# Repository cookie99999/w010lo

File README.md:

# A homebrew MC68010 computer

### Current specs:

- 16MHz 68010
- 1MB RAM
- 256K flash
- 68681 DUART
- A simple monitor ported from my 65816 computer, with XMODEM download support
- PATA interface (tested with several CF cards and a real IDE HDD)

### Todo:

- New PCB revision with some bodge fixes and some SMD parts to fit more memory
- Real-time clock
- Audio+video board
- PS/2 mouse + keyboard controller
- Consider networking (SLIP or ethernet controller)

### Toolchain notes

For assembly I am using vasm, since I like the syntax better than GAS. For C, I built a cross-compiling GCC and binutils from source. When configuring GCC for a 68000/68008/68010 target, you have to be careful not to let it use any 68020+ or FPU specific instructions, or else your libgcc won't work. Here's the line I used to configure mine:
```
../gcc-15.2.0/configure --prefix=/home/cookie/.local/ --program-prefix=m68k-elf- --target=m68k-elf --with-cpu=m68000 --enable-languages=c --with-newlib --disable-libssp --disable-libgomp --disable-threads --disable-multilib --disable-nls --disable-libquadmath --without-headers --disable-m68020 --disable-m68881
```
Some of the less obvious options may not be strictly necessary, I haven't tested with and without each one.
With just a compiler, binutils, and libgcc, you have pretty much all you need to comfortably write and use C programs. I have ported newlib+libgloss, but have some minor bugs to work out. I will eventually write up the process, as a lot of the documentation online is outdated by this point.

###

Shoutout to [aslak](https://www.aslak.net/), [rosco-m68k](https://github.com/rosco-m68k), [68-Katy](https://www.bigmessowires.com/68-katy/), [Matt Sarnoff](https://github.com/74hc595/68k-nano), [Jeff Tranter](https://jefftranter.blogspot.com/), and [Mackerel-68k](https://hackaday.io/project/183861-mackerel-68k-linux-sbcs) for their inspiring projects and helpful logs.

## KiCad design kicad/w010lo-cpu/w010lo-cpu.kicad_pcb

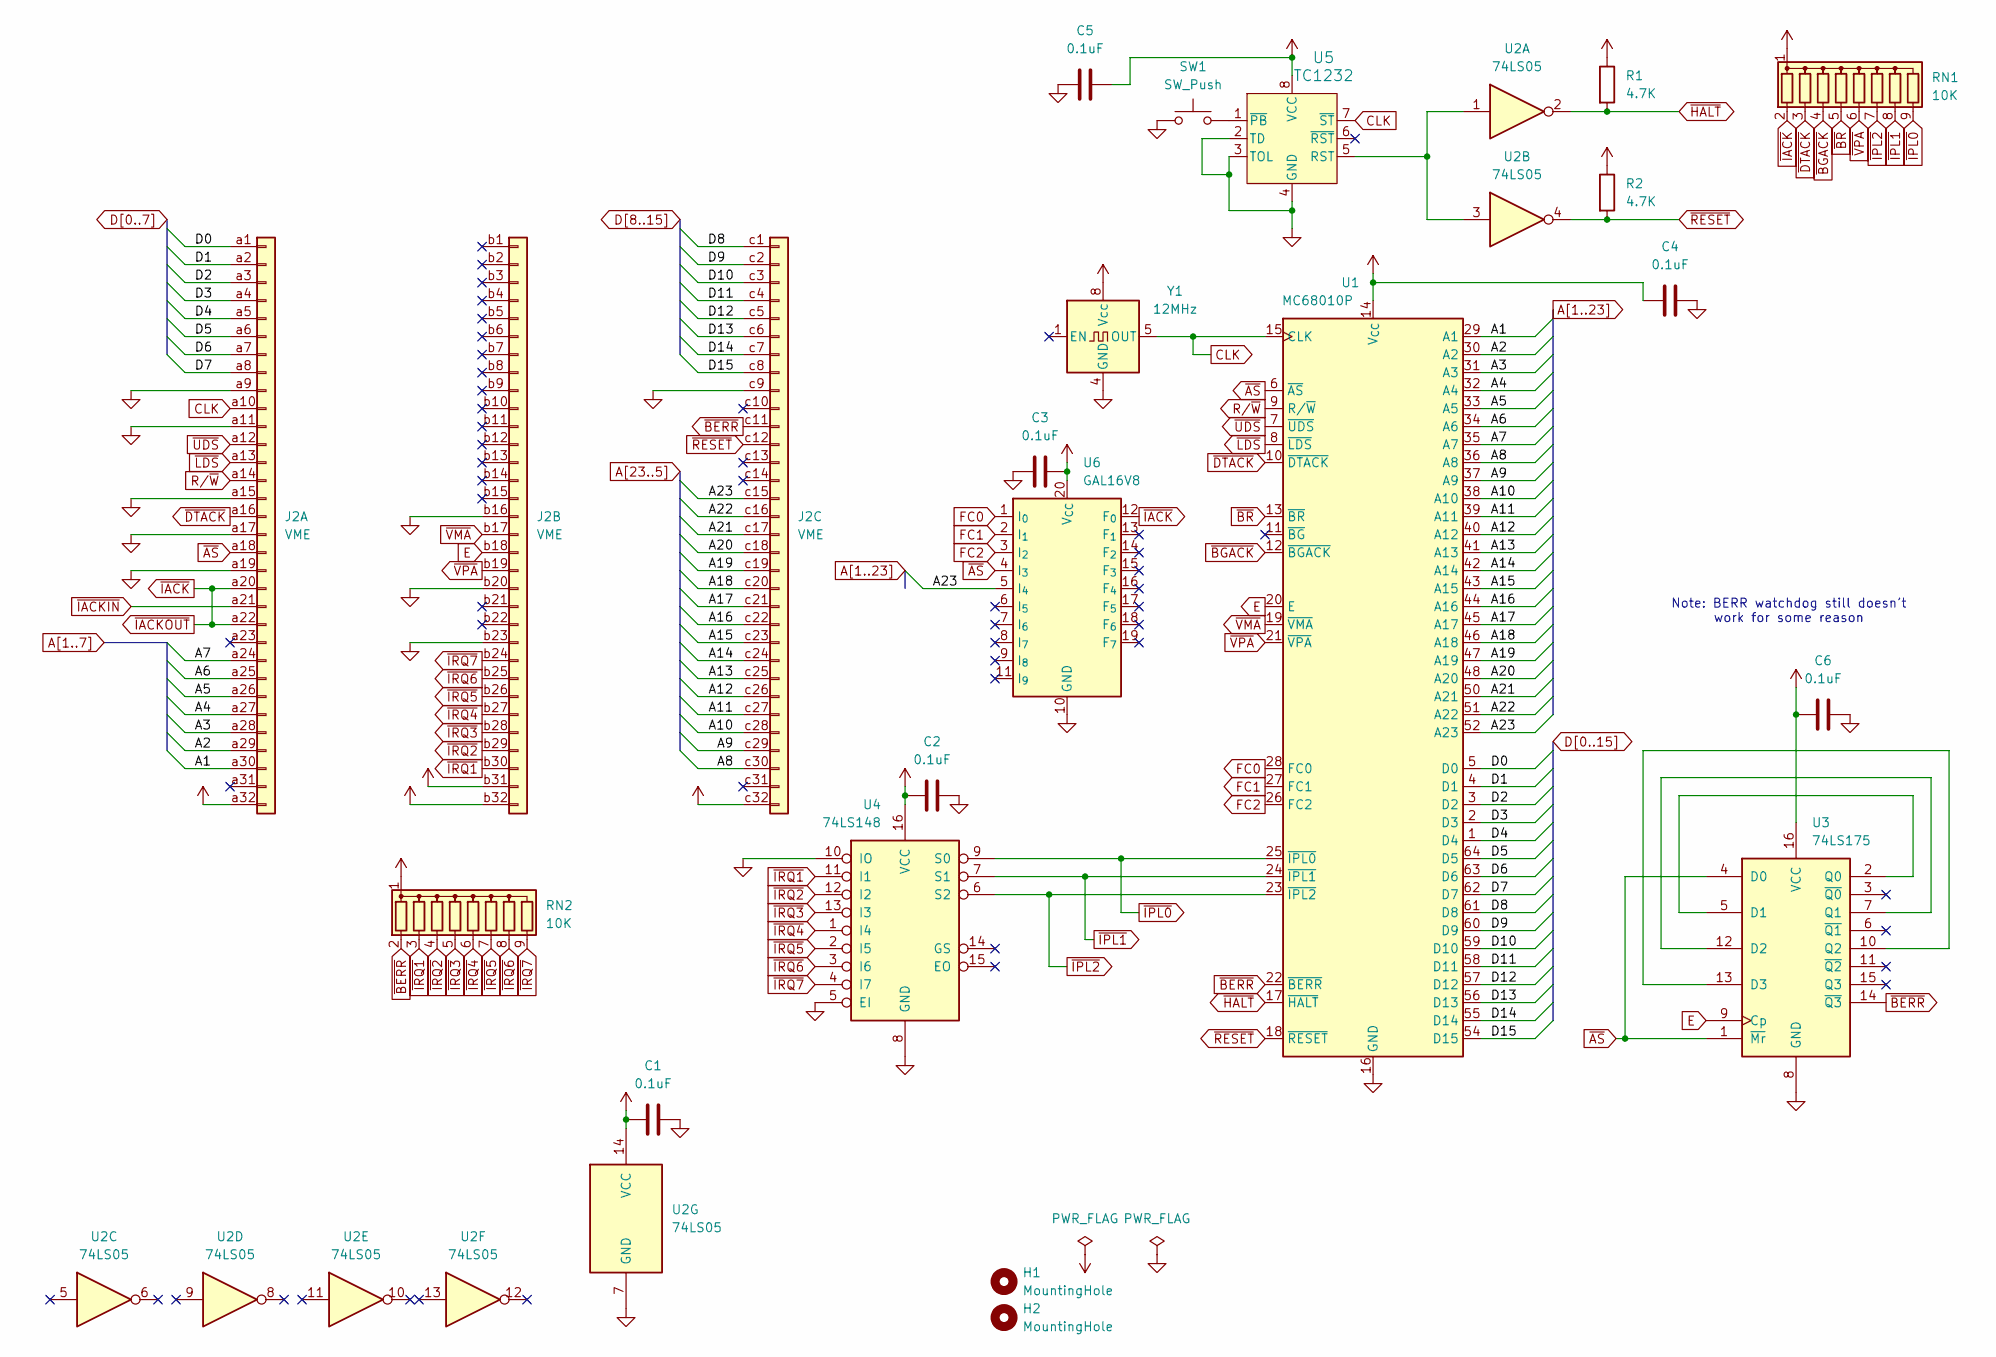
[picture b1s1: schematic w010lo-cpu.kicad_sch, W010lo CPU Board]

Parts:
C1, C2, C3, C4, C5, C6: 0.1uF; C_Disc_D5.0mm_W2.5mm_P5.00mm
H1, H2: MountingHole; MountingHole_3.2mm_M3
J2: VME; DIN41612_C_3x32_Male_Horizontal_THT
R1, R2: 4.7K; R_Axial_DIN0204_L3.6mm_D1.6mm_P5.08mm_Horizontal
RN1, RN2: 10K; R_Array_SIP9
SW1: SW_Push; SW_TS11-674-135-BK-160-RA-D
U1: MC68010P; DIP-64_W22.86mm
U2: 74LS05; DIP-14_W7.62mm_Socket
U3: 74LS175; DIP-16_W7.62mm_Socket
U4: 74LS148; DIP-16_W7.62mm_Socket
U5: TC1232; DIP-8_W7.62mm_Socket
U6: GAL16V8; DIP-20_W7.62mm_Socket
Y1: 12MHz; Oscillator_DIP-8

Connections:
A1: J2.a30, U1.29 (A1)
A2: J2.a29, U1.30 (A2)
A3: J2.a28, U1.31 (A3)
A4: J2.a27, U1.32 (A4)
A5: J2.a26, U1.33 (A5)
A6: J2.a25, U1.34 (A6)
A7: J2.a24, U1.35 (A7)
A8: J2.c30, U1.36 (A8)
A9: J2.c29, U1.37 (A9)
A10: J2.c28, U1.38 (A10)
A11: J2.c27, U1.39 (A11)
A12: J2.c26, U1.40 (A12)
A13: J2.c25, U1.41 (A13)
A14: J2.c24, U1.42 (A14)
A15: J2.c23, U1.43 (A15)
A16: J2.c22, U1.44 (A16)
A17: J2.c21, U1.45 (A17)
A18: J2.c20, U1.46 (A18)
A19: J2.c19, U1.47 (A19)
A20: J2.c18, U1.48 (A20)
A21: J2.c17, U1.50 (A21)
A22: J2.c16, U1.51 (A22)
A23: J2.c15, U1.52 (A23), U6.5 (I_{4})
CLK: J2.a10, U1.15 (CLK), U5.7 (~ST), Y1.5 (OUT)
D0: J2.a1, U1.5 (D0)
D1: J2.a2, U1.4 (D1)
D2: J2.a3, U1.3 (D2)
D3: J2.a4, U1.2 (D3)
D4: J2.a5, U1.1 (D4)
D5: J2.a6, U1.64 (D5)
D6: J2.a7, U1.63 (D6)
D7: J2.a8, U1.62 (D7)
D8: J2.c1, U1.61 (D8)
D9: J2.c2, U1.60 (D9)
D10: J2.c3, U1.59 (D10)
D11: J2.c4, U1.58 (D11)
D12: J2.c5, U1.57 (D12)
D13: J2.c6, U1.56 (D13)
D14: J2.c7, U1.55 (D14)
D15: J2.c8, U1.54 (D15)
E: J2.b18, U1.20 (E), U3.9 (Cp)
FC0: U1.28 (FC0), U6.1 (I_{0})
FC1: U1.27 (FC1), U6.2 (I_{1})
FC2: U1.26 (FC2), U6.3 (I_{2})
GND: C1.2, C2.2, C3.2, C4.2, C5.2, C6.2, J2.a9, J2.a11, J2.a15, J2.a17, J2.a19, J2.b16, J2.b20, J2.b23, J2.c9, SW1.1, U1.16 (GND), U1.53 (GND), U2.7 (GND), U3.8 (GND), U4.5 (EI), U4.8 (GND), U4.10 (IO), U5.2 (TD), U5.3 (TOL), U5.4 (GND), U6.10 (GND), Y1.4 (GND)
unnamed: U3.2 (Q0), U3.5 (D1)
unnamed: U3.7 (Q1), U3.12 (D2)
unnamed: U3.10 (Q2), U3.13 (D3)
unnamed: U2.1, U2.3, U5.5 (RST)
unnamed: SW1.2, U5.1 (~PB)
R/~W: J2.a14, U1.9 (R/~W)
VCC: C1.1, C2.1, C3.1, C4.1, C5.1, C6.1, J2.a32, J2.b31, J2.b32, J2.c32, R1.1, R2.1, RN1.1 (common), RN2.1 (common), U1.14 (V_{CC}), U1.49 (V_{CC}), U2.14 (VCC), U3.16 (VCC), U4.16 (VCC), U5.8 (VCC), U6.20 (V_{CC}), Y1.8 (Vcc)
~AS: J2.a18, U1.6 (~AS), U3.1 (~Mr), U3.4 (D0), U6.4 (I_{3})
~BERR: J2.c11, RN2.2 (R1), U1.22 (~BERR), U3.14 (~Q3)
~BGACK: RN1.4 (R3), U1.12 (~BGACK)
~BR: RN1.5 (R4), U1.13 (~BR)
~DTACK: J2.a16, RN1.3 (R2), U1.10 (~DTACK)
~HALT: R1.2, U1.17 (~HALT), U2.2
~IACKIN: J2.a21
~IACKOUT: J2.a20, J2.a22, RN1.2 (R1), U6.12 (F_{0})
~IPL0: RN1.9 (R8), U1.25 (~IPL0), U4.9 (S0)
~IPL1: RN1.8 (R7), U1.24 (~IPL1), U4.7 (S1)
~IPL2: RN1.7 (R6), U1.23 (~IPL2), U4.6 (S2)
~IRQ1: J2.b30, RN2.3 (R2), U4.11 (I1)
~IRQ2: J2.b29, RN2.4 (R3), U4.12 (I2)
~IRQ3: J2.b28, RN2.5 (R4), U4.13 (I3)
~IRQ4: J2.b27, RN2.6 (R5), U4.1 (I4)
~IRQ5: J2.b26, RN2.7 (R6), U4.2 (I5)
~IRQ6: J2.b25, RN2.8 (R7), U4.3 (I6)
~IRQ7: J2.b24, RN2.9 (R8), U4.4 (I7)
~LDS: J2.a13, U1.8 (~LDS)
~RESET: J2.c12, R2.2, U1.18 (~RESET), U2.4
~UDS: J2.a12, U1.7 (~UDS)
~VMA: J2.b17, U1.19 (~VMA)
~VPA: J2.b19, RN1.6 (R5), U1.21 (~VPA)

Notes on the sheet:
Note: BERR watchdog still doesn't work for some reason

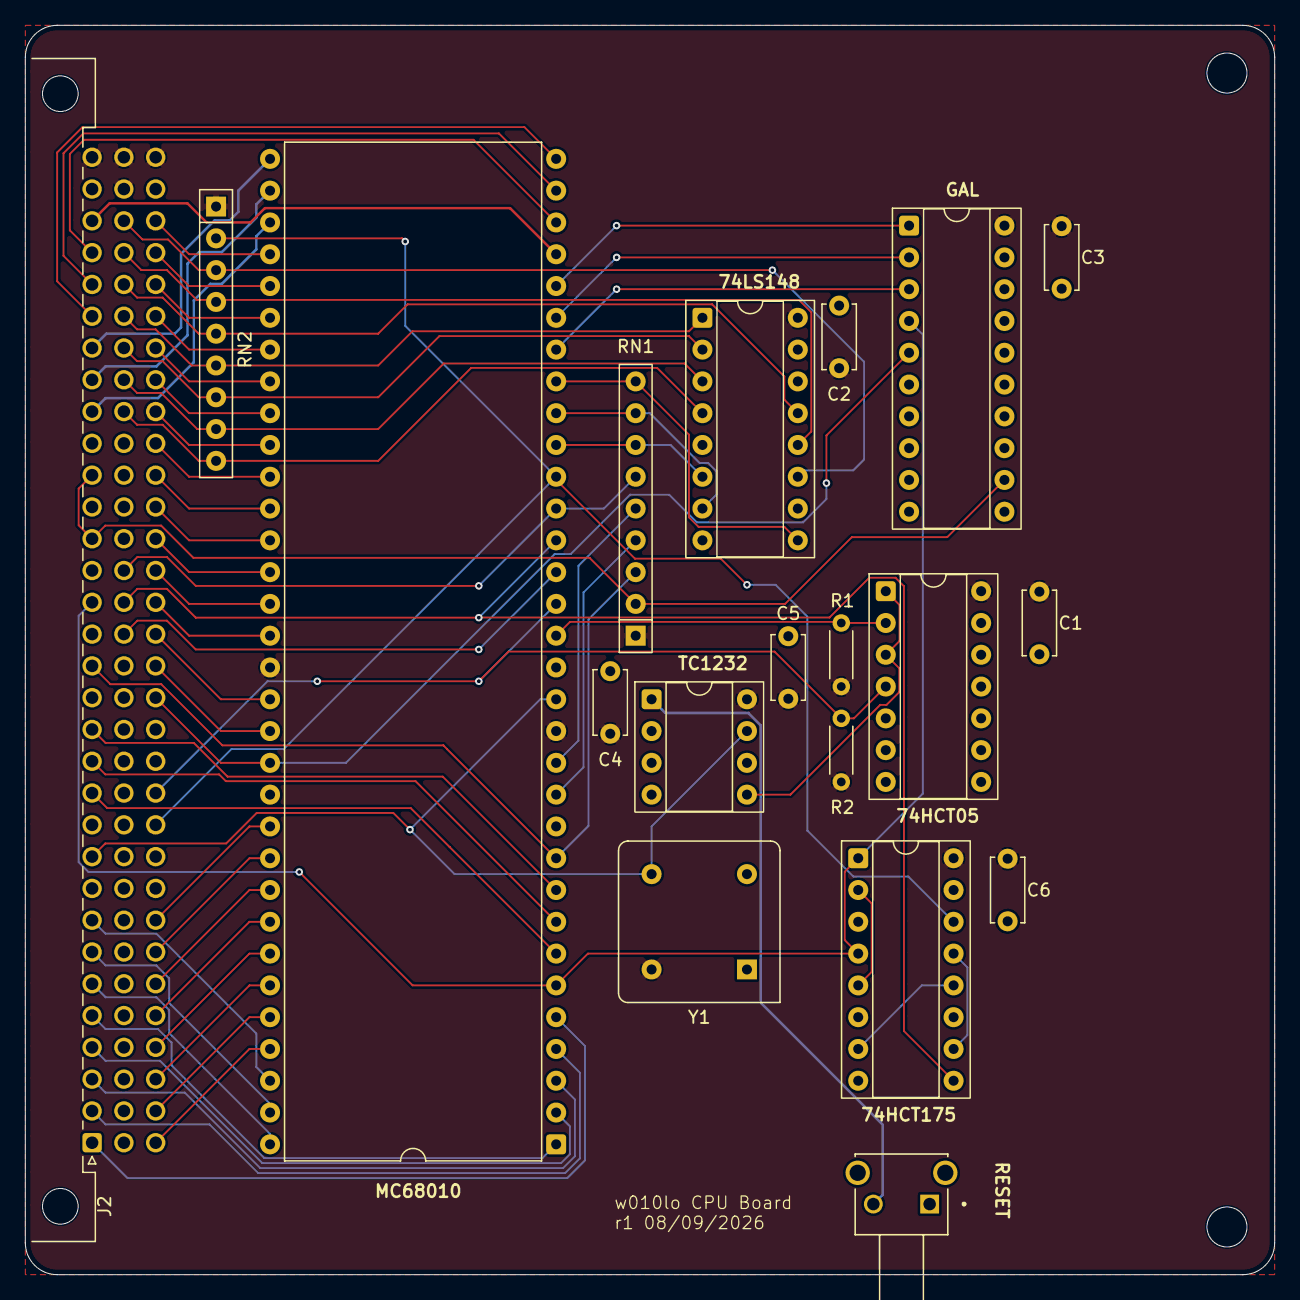
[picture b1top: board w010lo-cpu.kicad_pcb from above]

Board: 4 copper layers, 99.8 x 99.8 mm, 22 parts (0 on the bottom side), 74 nets.

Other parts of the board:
H3: MountingHole; MountingHole_3.2mm_M3

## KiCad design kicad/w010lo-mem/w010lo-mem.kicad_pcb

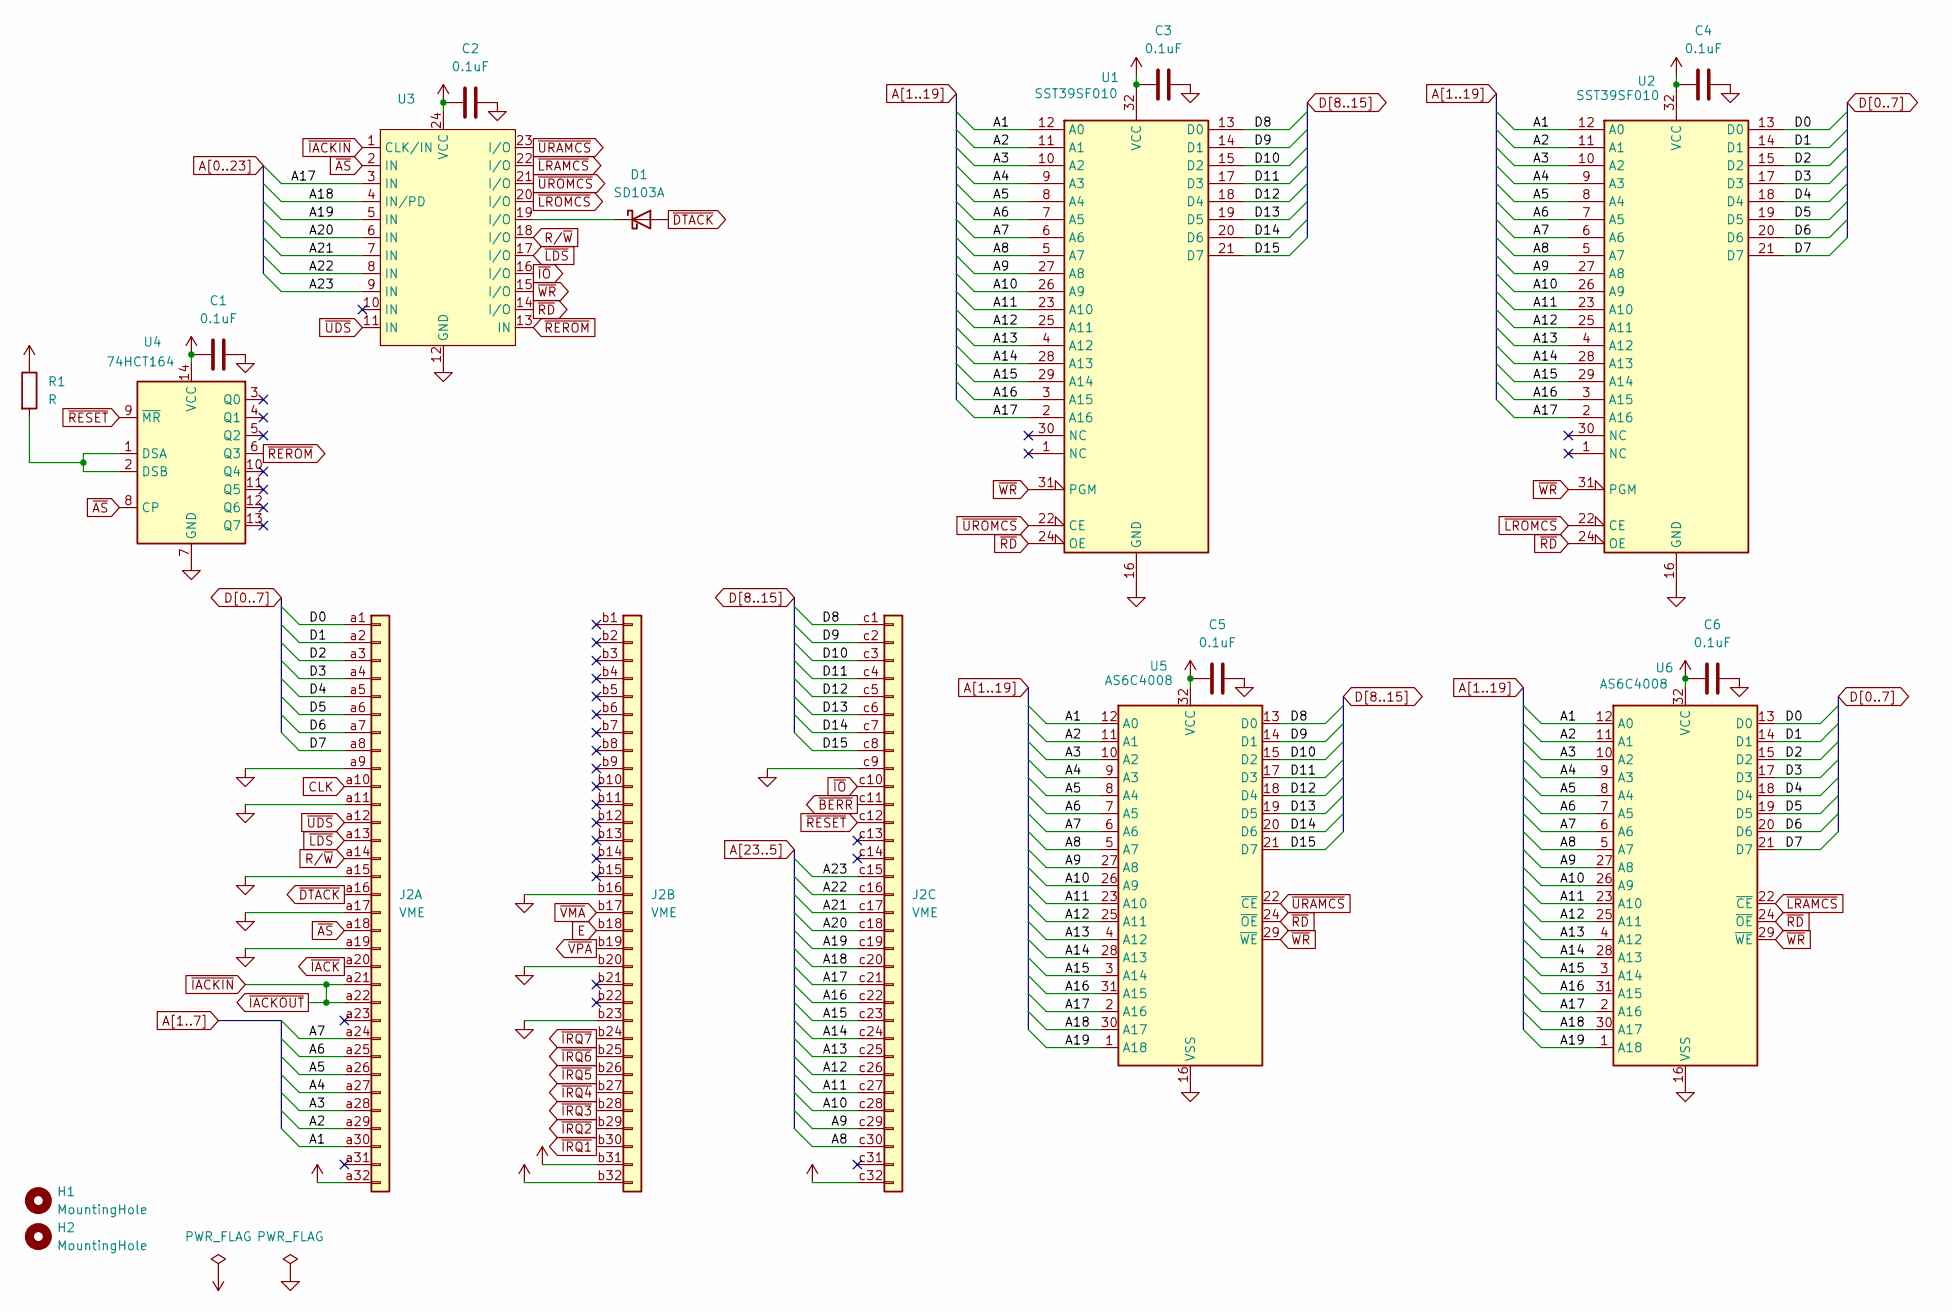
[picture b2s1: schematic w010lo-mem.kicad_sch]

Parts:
C1, C2, C3, C4, C5, C6: 0.1uF; C_Disc_D5.0mm_W2.5mm_P5.00mm
D1: SD103A; D_DO-35_SOD27_P7.62mm_Horizontal
H1, H2: MountingHole; MountingHole_3.2mm_M3
J2: VME; DIN41612_C_3x32_Male_Horizontal_THT
R1: R; R_Axial_DIN0207_L6.3mm_D2.5mm_P7.62mm_Horizontal
U1, U2: SST39SF010; DIP-32_W15.24mm_Socket
U3: DIP-24_W7.62mm_Socket
U4: 74HCT164; DIP-14_W7.62mm_Socket
U5, U6: AS6C4008; DIP-32_W15.24mm_Socket

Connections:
A1: J2.a30, U1.12 (A0), U2.12 (A0), U5.12 (A0), U6.12 (A0)
A2: J2.a29, U1.11 (A1), U2.11 (A1), U5.11 (A1), U6.11 (A1)
A3: J2.a28, U1.10 (A2), U2.10 (A2), U5.10 (A2), U6.10 (A2)
A4: J2.a27, U1.9 (A3), U2.9 (A3), U5.9 (A3), U6.9 (A3)
A5: J2.a26, U1.8 (A4), U2.8 (A4), U5.8 (A4), U6.8 (A4)
A6: J2.a25, U1.7 (A5), U2.7 (A5), U5.7 (A5), U6.7 (A5)
A7: J2.a24, U1.6 (A6), U2.6 (A6), U5.6 (A6), U6.6 (A6)
A8: J2.c30, U1.5 (A7), U2.5 (A7), U5.5 (A7), U6.5 (A7)
A9: J2.c29, U1.27 (A8), U2.27 (A8), U5.27 (A8), U6.27 (A8)
A10: J2.c28, U1.26 (A9), U2.26 (A9), U5.26 (A9), U6.26 (A9)
A11: J2.c27, U1.23 (A10), U2.23 (A10), U5.23 (A10), U6.23 (A10)
A12: J2.c26, U1.25 (A11), U2.25 (A11), U5.25 (A11), U6.25 (A11)
A13: J2.c25, U1.4 (A12), U2.4 (A12), U5.4 (A12), U6.4 (A12)
A14: J2.c24, U1.28 (A13), U2.28 (A13), U5.28 (A13), U6.28 (A13)
A15: J2.c23, U1.29 (A14), U2.29 (A14), U5.3 (A14), U6.3 (A14)
A16: J2.c22, U1.3 (A15), U2.3 (A15), U5.31 (A15), U6.31 (A15)
A17: J2.c21, U1.2 (A16), U2.2 (A16), U3.3 (IN), U5.2 (A16), U6.2 (A16)
A18: J2.c20, U3.4 (IN/PD), U5.30 (A17), U6.30 (A17)
A19: J2.c19, U3.5 (IN), U5.1 (A18), U6.1 (A18)
A20: J2.c18, U3.6 (IN)
A21: J2.c17, U3.7 (IN)
A22: J2.c16, U3.8 (IN)
A23: J2.c15, U3.9 (IN)
CLK: J2.a10
D0: J2.a1, U2.13 (D0), U6.13 (D0)
D1: J2.a2, U2.14 (D1), U6.14 (D1)
D2: J2.a3, U2.15 (D2), U6.15 (D2)
D3: J2.a4, U2.17 (D3), U6.17 (D3)
D4: J2.a5, U2.18 (D4), U6.18 (D4)
D5: J2.a6, U2.19 (D5), U6.19 (D5)
D6: J2.a7, U2.20 (D6), U6.20 (D6)
D7: J2.a8, U2.21 (D7), U6.21 (D7)
D8: J2.c1, U1.13 (D0), U5.13 (D0)
D9: J2.c2, U1.14 (D1), U5.14 (D1)
D10: J2.c3, U1.15 (D2), U5.15 (D2)
D11: J2.c4, U1.17 (D3), U5.17 (D3)
D12: J2.c5, U1.18 (D4), U5.18 (D4)
D13: J2.c6, U1.19 (D5), U5.19 (D5)
D14: J2.c7, U1.20 (D6), U5.20 (D6)
D15: J2.c8, U1.21 (D7), U5.21 (D7)
E: J2.b18
GND: C1.2, C2.2, C3.2, C4.2, C5.2, C6.2, J2.a9, J2.a11, J2.a15, J2.a17, J2.a19, J2.b16, J2.b20, J2.b23, J2.c9, U1.16 (GND), U2.16 (GND), U3.12 (GND), U4.7 (GND), U5.16 (VSS), U6.16 (VSS)
unnamed: D1.1 (K), U3.19 (I/O)
unnamed: R1.2, U4.1 (DSA), U4.2 (DSB)
R/~W: J2.a14, U3.18 (I/O)
VCC: C1.1, C2.1, C3.1, C4.1, C5.1, C6.1, J2.a32, J2.b31, J2.b32, J2.c32, R1.1, U1.32 (VCC), U2.32 (VCC), U3.24 (VCC), U4.14 (VCC), U5.32 (VCC), U6.32 (VCC)
~AS: J2.a18, U3.2 (IN), U4.8 (CP)
~BERR: J2.c11
~DTACK: D1.2 (A), J2.a16
~IACKIN: J2.a21, J2.a22, U3.1 (CLK/IN)
~IACK: J2.a20
~IO: J2.c10, U3.16 (I/O)
~IRQ1: J2.b30
~IRQ2: J2.b29
~IRQ3: J2.b28
~IRQ4: J2.b27
~IRQ5: J2.b26
~IRQ6: J2.b25
~IRQ7: J2.b24
~LDS: J2.a13, U3.17 (I/O)
~LRAMCS: U3.22 (I/O), U6.22 (~CE)
~LROMCS: U2.22 (CE), U3.20 (I/O)
~RD: U1.24 (OE), U2.24 (OE), U3.14 (I/O), U5.24 (~OE), U6.24 (~OE)
~REROM: U3.13 (IN), U4.6 (Q3)
~RESET: J2.c12, U4.9 (~MR)
~UDS: J2.a12, U3.11 (IN)
~URAMCS: U3.23 (I/O), U5.22 (~CE)
~UROMCS: U1.22 (CE), U3.21 (I/O)
~VMA: J2.b17
~VPA: J2.b19
~WR: U1.31 (PGM), U2.31 (PGM), U3.15 (I/O), U5.29 (~WE), U6.29 (~WE)

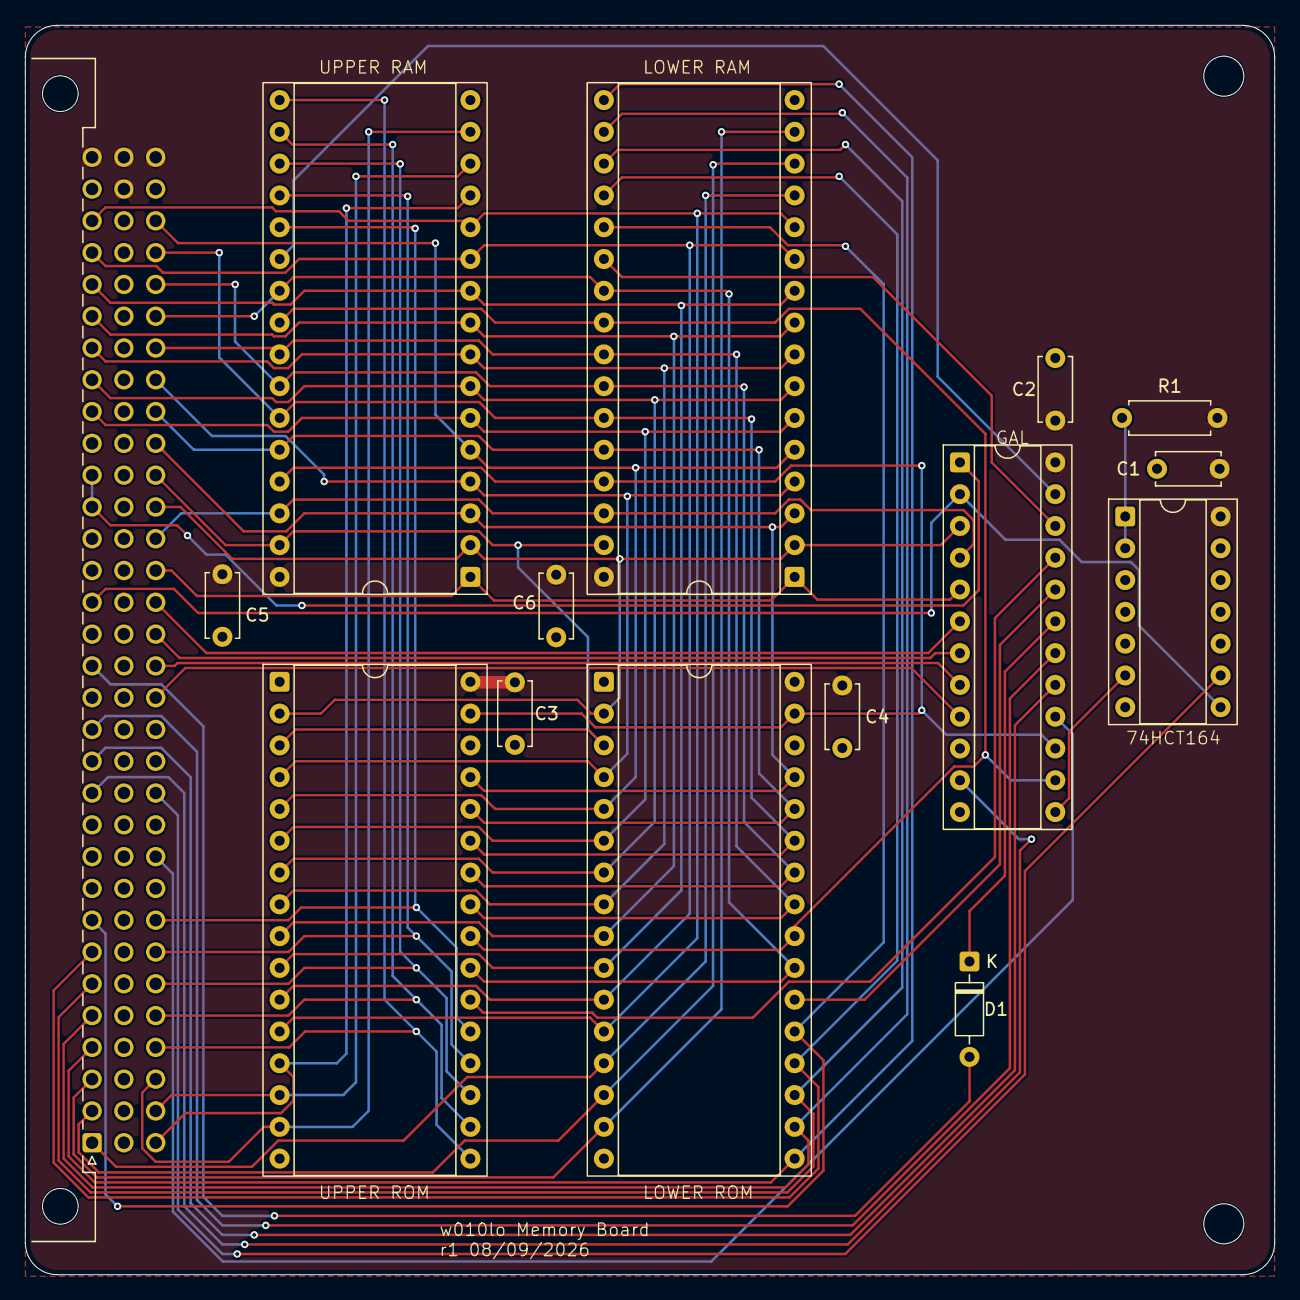
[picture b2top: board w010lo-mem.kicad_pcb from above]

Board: 4 copper layers, 99.8 x 99.8 mm, 17 parts (0 on the bottom side), 58 nets.

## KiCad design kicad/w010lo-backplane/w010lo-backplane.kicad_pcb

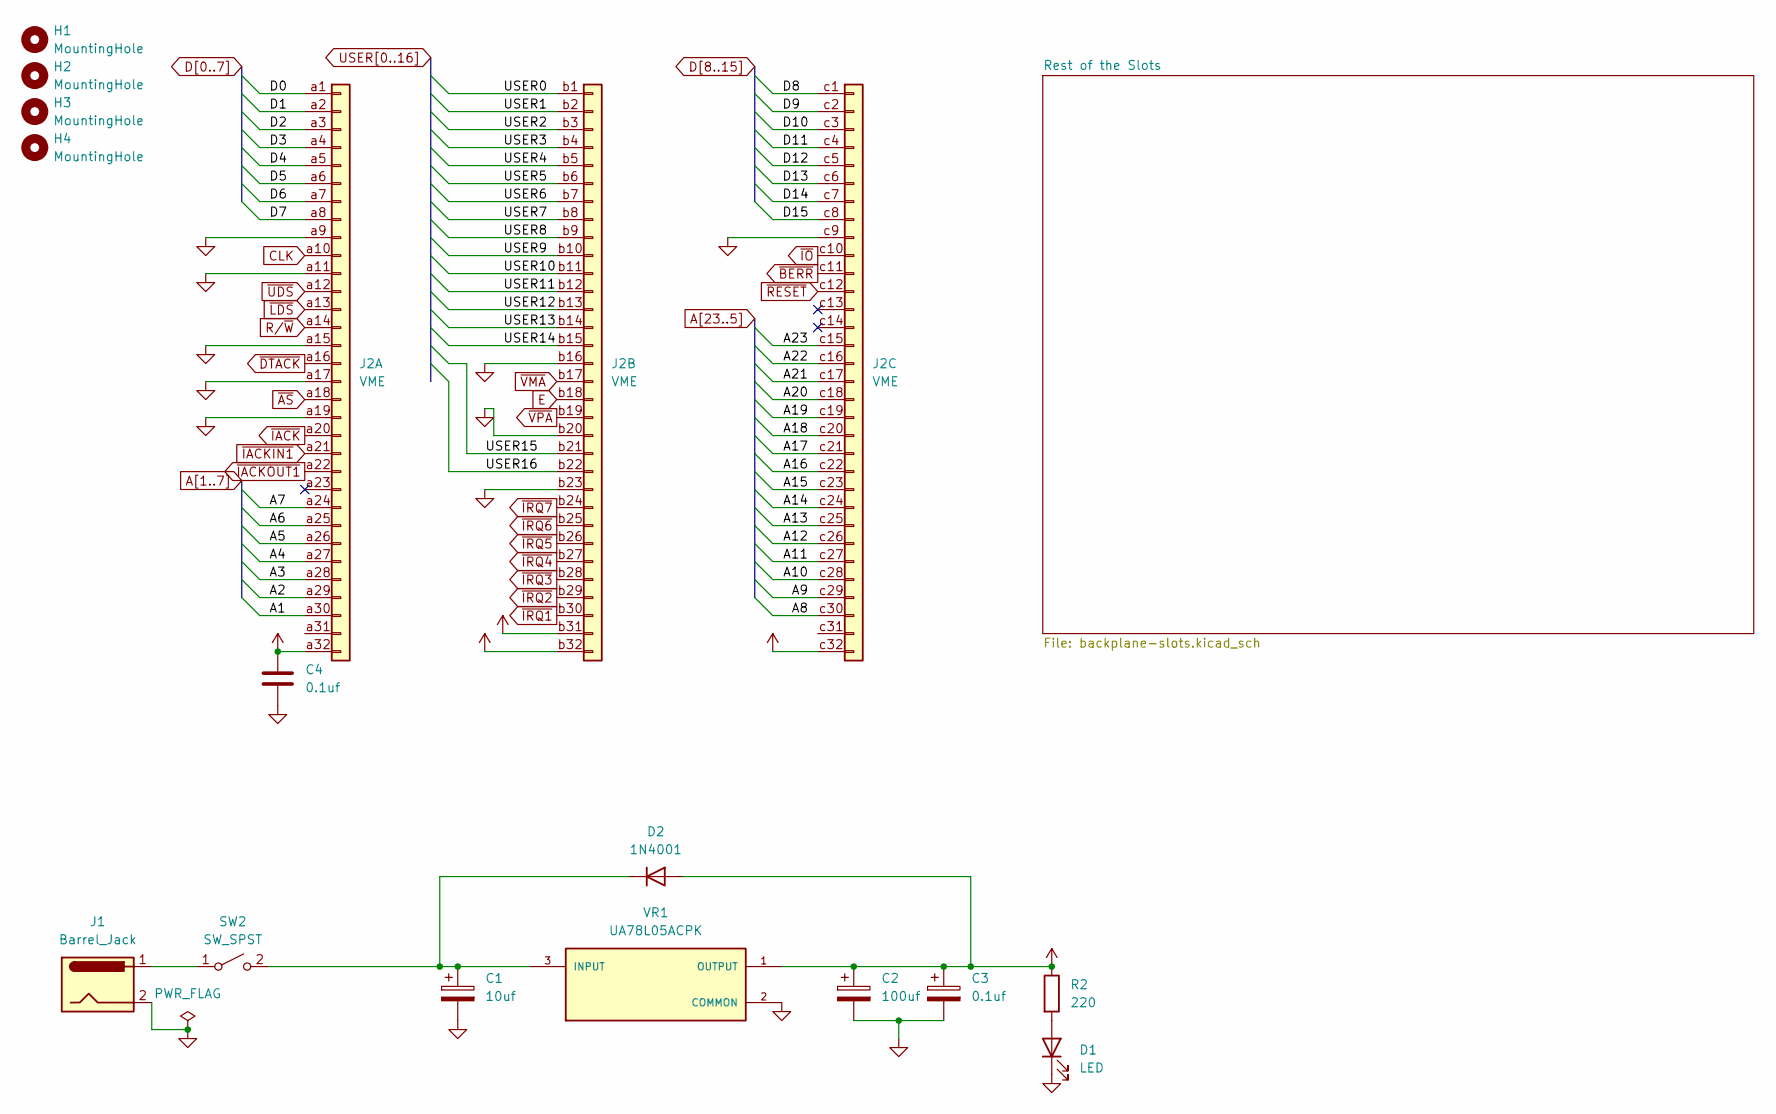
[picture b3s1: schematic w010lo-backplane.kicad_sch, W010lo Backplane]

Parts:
C1: 10uf; CP_Radial_D5.0mm_P2.50mm
C2: 100uf; CP_Radial_D5.0mm_P2.50mm
C3, C4: 0.1uf; C_Disc_D5.0mm_W2.5mm_P5.00mm
D1: LED; LED_D5.0mm
D2: 1N4001; D_DO-41_SOD81_P10.16mm_Horizontal
H1, H2, H3, H4: MountingHole; MountingHole_3.2mm_M3
J1: Barrel_Jack; BarrelJack_Horizontal
J2: VME; DIN41612_C_3x32_Female_Vertical_THT
R2: 220; R_Axial_DIN0207_L6.3mm_D2.5mm_P7.62mm_Horizontal
SW2: SW_SPST; SW_Slide_SPDT_Straight_CK_OS102011MS2Q
VR1: UA78L05ACPK; TO-220-3_Vertical; PARTREV V

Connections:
A1: J2.a30; also elsewhere on the board
A2: J2.a29; also elsewhere on the board
A3: J2.a28; also elsewhere on the board
A4: J2.a27; also elsewhere on the board
A5: J2.a26; also elsewhere on the board
A6: J2.a25; also elsewhere on the board
A7: J2.a24; also elsewhere on the board
A8: J2.c30; also elsewhere on the board
A9: J2.c29; also elsewhere on the board
A10: J2.c28; also elsewhere on the board
A11: J2.c27; also elsewhere on the board
A12: J2.c26; also elsewhere on the board
A13: J2.c25; also elsewhere on the board
A14: J2.c24; also elsewhere on the board
A15: J2.c23; also elsewhere on the board
A16: J2.c22; also elsewhere on the board
A17: J2.c21; also elsewhere on the board
A18: J2.c20; also elsewhere on the board
A19: J2.c19; also elsewhere on the board
A20: J2.c18; also elsewhere on the board
A21: J2.c17; also elsewhere on the board
A22: J2.c16; also elsewhere on the board
A23: J2.c15; also elsewhere on the board
CLK: J2.a10; also elsewhere on the board
D0: J2.a1; also elsewhere on the board
D1: J2.a2; also elsewhere on the board
D2: J2.a3; also elsewhere on the board
D3: J2.a4; also elsewhere on the board
D4: J2.a5; also elsewhere on the board
D5: J2.a6; also elsewhere on the board
D6: J2.a7; also elsewhere on the board
D7: J2.a8; also elsewhere on the board
D8: J2.c1; also elsewhere on the board
D9: J2.c2; also elsewhere on the board
D10: J2.c3; also elsewhere on the board
D11: J2.c4; also elsewhere on the board
D12: J2.c5; also elsewhere on the board
D13: J2.c6; also elsewhere on the board
D14: J2.c7; also elsewhere on the board
D15: J2.c8; also elsewhere on the board
E: J2.b18; also elsewhere on the board
GND: C1.2, C2.2, C3.2, C4.2, D1.1 (K), J1.2, J2.a9, J2.a11, J2.a15, J2.a17, J2.a19, J2.b16, J2.b20, J2.b23, J2.c9, VR1.2 (COMMON); also elsewhere on the board
unnamed: D1.2 (A), R2.2
unnamed: C1.1, D2.1 (K), SW2.2 (B), VR1.3 (INPUT)
unnamed: J1.1, SW2.1 (A)
R/~W: J2.a14; also elsewhere on the board
USER0: J2.b1; also elsewhere on the board
USER1: J2.b2; also elsewhere on the board
USER2: J2.b3; also elsewhere on the board
USER3: J2.b4; also elsewhere on the board
USER4: J2.b5; also elsewhere on the board
USER5: J2.b6; also elsewhere on the board
USER6: J2.b7; also elsewhere on the board
USER7: J2.b8; also elsewhere on the board
USER8: J2.b9; also elsewhere on the board
USER9: J2.b10; also elsewhere on the board
USER10: J2.b11; also elsewhere on the board
USER11: J2.b12; also elsewhere on the board
USER12: J2.b13; also elsewhere on the board
USER13: J2.b14; also elsewhere on the board
USER14: J2.b15; also elsewhere on the board
USER15: J2.b21; also elsewhere on the board
USER16: J2.b22; also elsewhere on the board
VCC: C2.1, C3.1, C4.1, D2.2 (A), J2.a32, J2.b31, J2.b32, J2.c32, R2.1, VR1.1 (OUTPUT); also elsewhere on the board
~AS: J2.a18; also elsewhere on the board
~BERR: J2.c11; also elsewhere on the board
~DTACK: J2.a16; also elsewhere on the board
~IACKIN1: J2.a21
~IACKOUT1: J2.a22; also elsewhere on the board
~IACK: J2.a20; also elsewhere on the board
~IO: J2.c10; also elsewhere on the board
~IRQ1: J2.b30; also elsewhere on the board
~IRQ2: J2.b29; also elsewhere on the board
~IRQ3: J2.b28; also elsewhere on the board
~IRQ4: J2.b27; also elsewhere on the board
~IRQ5: J2.b26; also elsewhere on the board
~IRQ6: J2.b25; also elsewhere on the board
~IRQ7: J2.b24; also elsewhere on the board
~LDS: J2.a13; also elsewhere on the board
~RESET: J2.c12; also elsewhere on the board
~UDS: J2.a12; also elsewhere on the board
~VMA: J2.b17; also elsewhere on the board
~VPA: J2.b19; also elsewhere on the board
